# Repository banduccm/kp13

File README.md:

# Keypad #

This is an attempt to design a serviceable replacement the long-discontinued G13 "gameboard".

## PCB ##

The PCB design depends on symbols from a few libraries:

- <https://github.com/stormbard/Keyboard.pretty> for the hotswap switch footprints
- <https://github.com/drewgates/kb2040-kicad> for the Adafruit KB2040 footprint, symbol, and step file
- <https://grabcad.com/library/kailh-hotswap-mx-1> for the hot-swap socket step file (requires registration)

### Board Layout ###

The G13 had 22 "G" keys, 2 thumb keys, and an analog stick with a click (in addition to some other buttons not
important to this effort).

This initial project contains the main board with 22 keys and 2 pushbuttons intended to be used to switch
layers in QMK. It also includes a header with 2 rows and 6 columns for an expansion board (i.e, the thumb
buttons).

The KB2040 was selected due to easy availability, compatibility with the Pro Micro pinout, and a USB-C port.
Other Pro Micro-compatible boards may work, but take care to skip the D+/D- pins from the KB2040.

## Plates ##

The switch mounting plates for this project were initially designed using swillkb's
[Plate & Case Builder](http://builder.swillkb.com/) tool, then imported into qcad for manipulation.

Experimental baseplates for both the keypad and full-size thumb pod are included, as are 3d-printable spacers
to sit between the plates and PCB.

### Keyboard Layout ###

This layout is used by both the plate builder and the
[Keyboard Layout Editor](http://www.keyboard-layout-editor.com) tool:

```text
[{x:3}, "C0", "C1"],
["G1","G2","G3","G4","G5","G6","G7"],
["G8","G9","G10","G11","G12","G13","G14"],
[{x:0.75,w:1.25},"G15","G16","G17","G18",{w:1.25},"G19"],
[{x:1,w:2},"G20","G21",{w:2},"G22"],
[{x:8.75}, "Stick ↑"],
[{x:7.25}, "G23", "Stick ←", "Stick →"],
[{x:7}, "G24", {x:0.75}, "Stick ↓" ],
[{x:8}, "G25", "G26"]
```

For Via (with some extra design flavor), this is:

```text
[{x:3},"3,4","3,5"],
["0,0","0,1","0,2","0,3","0,4","0,5","1,0"],
["1,1","1,2","1,3","1,4","1,5","2,0","2,1"],
[{x:0.75,w:1.25},"2,2","2,3","2,4","2,5",{w:1.25},"3,0"],
[{x:1,w:2},"3,1","3,2",{w:2},"3,3"],
[{y:0.75,x:8.75,h:0.75},"4,0"],
[{y:-0.75,x:7.25},"5,0"],
[{y:-0.5,x:8.25,h:0.75},"4,1",{h:0.75},"4,3"],
[{y:-0.5,x:7},"5,1"],
[{y:-0.75,x:8.75,h:0.75},"4,2"],
[{y:-0.25,x:8},"5,2","5,3"]

```

 ## Parts ##

 For the first build, the following parts were used:

 ### Plate ###

 The place was ordered from [SendCutSend](https://sendcutsend.com/) in 1.6mm thick 5051 Aluminum.

 ### Electronics ###

 Initial parts were ordered from Adafruit:

- 30x [1N4148 diodes](https://www.adafruit.com/product/1641)
- 20x [6mm Tactile Button switch](https://www.adafruit.com/product/367)
- 40x [Kailh Switch Sockets for MX-compatible Mechanical Keys](https://www.adafruit.com/product/4958)
- 30x [Kailh Mechanical Key Switches - Linear Black](https://www.adafruit.com/product/4953)
- 1x [Adafruit KB2040](https://www.adafruit.com/product/5302)
- ~~1x [GMK Screw-in Stabilizers](https://1upkeyboards.com/shop/parts-and-tools/parts/gmk-screw-in-stabilizers/)~~ _Note: These ended up being incompatible with the plate, see v0.1.0 notes_
- 1x [Durock Plate Mount Stabilizers](https://1upkeyboards.com/shop/parts-and-tools/parts/durock-plate-mount-stabilizers-60-tkl-piano/)

### PCB ###

The PCB was ordered from PCBWay using their Kicad plugin.

## Version Notes ##

### v0.1.0 ###

Generally good news! The parts all fit as expected and the circuit works as designed. No reworks required to
have a functioning 22-key setup.

- The plate is not compatible with the PCB-mount stabilizers.
- The angle on the plate and the angle on the PCB are not the same. This is annoying, but not a functional
 problem.
- n-key rollover works (as expected), but note that QMK defaults to 6KRO. The default keymap uses switch C0
 on Layer 0 to toggle it.

### v0.1.1 ###

Instead of relying on trying to rely on external tools, all the mechanical bits were re-drawn in qcad, which
helpfully makes it extremely simple to import an exported .dxf from KiCAD for tracing and fit checking. The
stabilizer compatibility was not addressed (yet), but at least the angle between the PCB and plate(s) now
aligns.

## v0.2.0 Wishlist ##

During the mechanical design phase, some items were added as a wishlist for a potential second spin of the
"big" board:

- Smaller, optimized thumb-pod connector. Considering using a 1.27mm pitch 10-pin cable (Cortex-M SWD
  connector) to reduce mechanical size.
- Figure out how to use the kb2040's castellated pins to reduce z-height

## Thumb Pods ##

The thumb pod(s) incorporate a 4-way (with diagonals!) thumbstick and 0-4 buttons. There are 2 different
versions: regular (4x 1U MX switch, 1x thumbstick) and mini (2x microswitch, 1x thumbstick). The thumbstick
uses the same matrix positions on each version, so it is possible to populate multiple pods and swap between
them as desired.

The pods feature a notched edge for mounting square against the keypad PCB (or a case holding it). This
ensures the A/B/C/D positions of the thumbstick are square with the keypad.

### Thumbstick ###

- [ALPS RKJXM1015004](https://tech.alpsalpine.com/e/products/detail/RKJXM1015004/)

This thumbstick has 4 switches and can handle diagonal movements as well. It has a "stick click", but this
is not broken out as a dedicated pin, so it's unclear if it is compatible with QMK. In v0.1 of the thumb
pods, the "push" pins are not connected to the key matrix. The "push" pins _are_ on their own net, however,
so they could be hand-wired into the matrix if desired. The same thumbstick is used for both thumb pod
designs.

### Thumb Pod (full size) ###

The regular thumb pod uses the same MX hot-swap sockets and 1U keys as the main keypad to provide 4 switches
surrounding the thumbstick.

Experimental top and bottom plates are provided for the full-size thumb pod.

### Thumb Pod Mini ###

The mini thumb pod closely approximates the original G13 thumb section: two mouse-like microswitches and the
thumbstick. This version will require some sort of housing, as it's not really feasible to hit microswitch
actuators.

#### Electronics ####

- [Kailh GM Microswitch](https://www.kailhswitch.com/micro-switches/mouse-micro-switches/high-click-life-gaming-micro-mouse-switch.html)

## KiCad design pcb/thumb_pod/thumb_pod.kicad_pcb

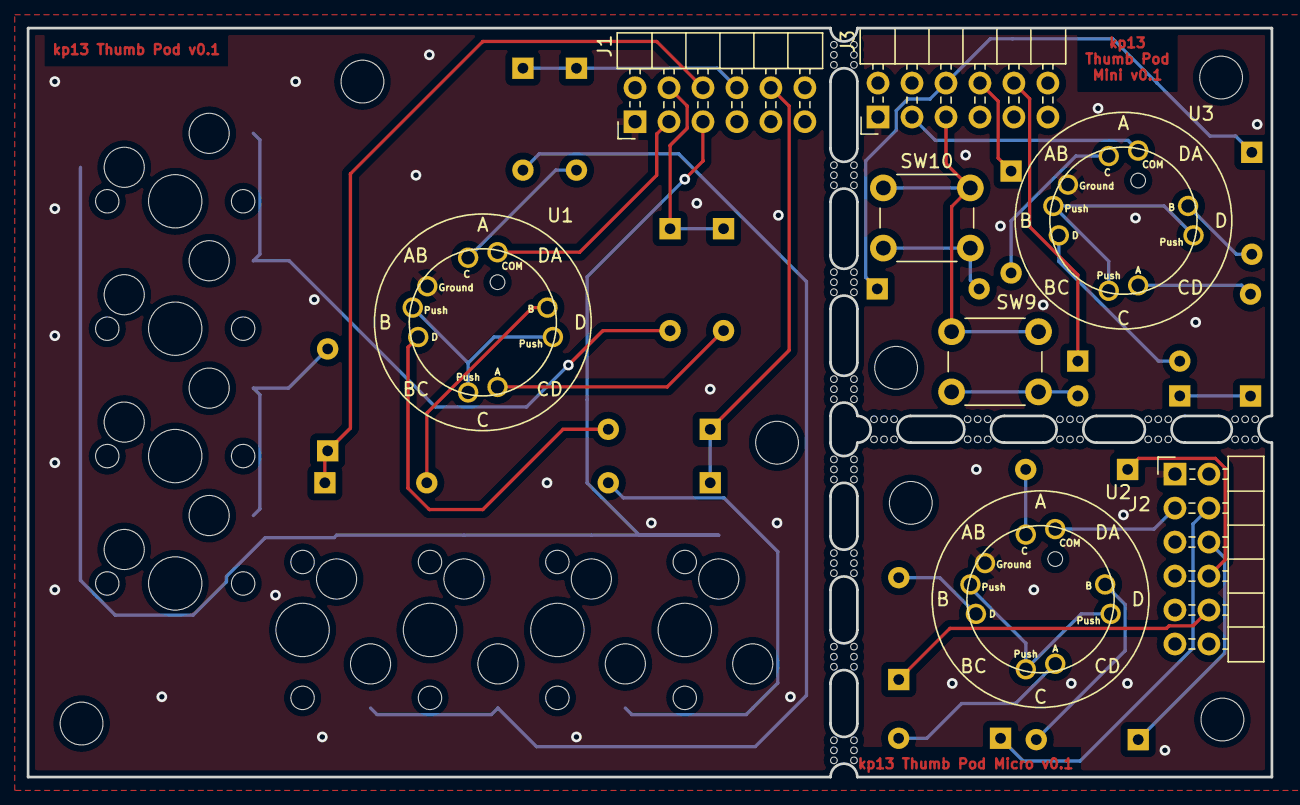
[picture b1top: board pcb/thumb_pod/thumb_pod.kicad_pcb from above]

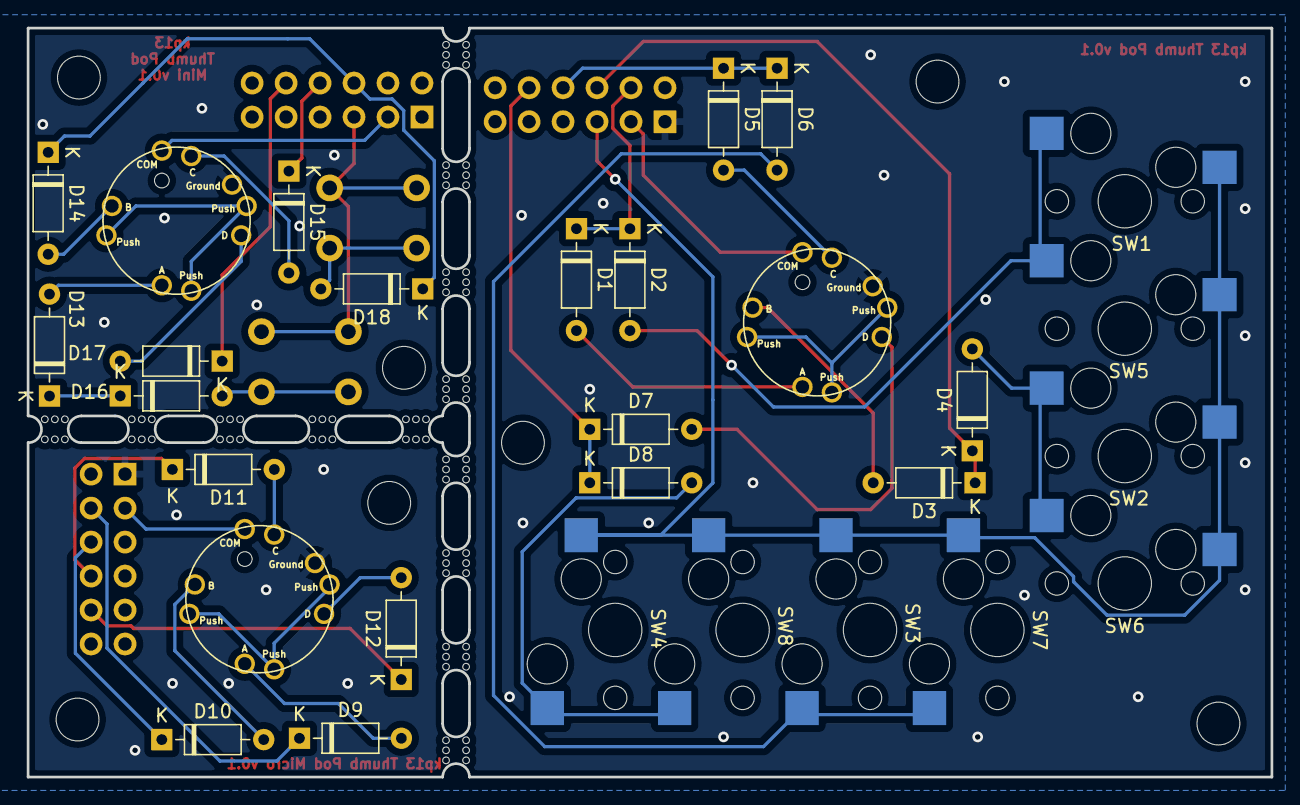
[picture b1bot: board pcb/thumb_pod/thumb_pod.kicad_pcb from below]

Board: 2 copper layers, 93.0 x 56.0 mm, 54 parts (18 on the bottom side), 28 nets.

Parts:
D1, D2, D3, D4, D5, D6, D7, D8, D9, D10, D11, D12, D13, D14, D15, D16, D17, D18: 1N4148; D_DO-35_SOD27_P7.62mm_Horizontal
H1, H2, H3, H4, H5, H6, H7: MountingHole; MountingHole_3.2mm_M3
J1, J2, J3: Conn_02x06_Odd_Even; PinHeader_2x06_P2.54mm_Horizontal
SW1, SW2, SW3, SW4, SW5, SW6, SW7, SW8: SW_Push; MXOnly-1U-Hotswap
SW9, SW10: SW_Push; SW_PUSH_6mm
U1, U2, U3: RKJXM1015004
mouse-bite-2mm-slot, mouse-bite-2mm-slot#2, mouse-bite-2mm-slot#3, mouse-bite-2mm-slot#4, mouse-bite-2mm-slot#5, mouse-bite-2mm-slot#6, mouse-bite-2mm-slot#7, mouse-bite-2mm-slot#8, mouse-bite-2mm-slot#9, mouse-bite-2mm-slot#10, mouse-bite-2mm-slot#11, mouse-bite-2mm-slot#12, mouse-bite-2mm-slot#13: VAL**; mouse-bite-2mm-slot

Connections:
/3.3v: J1.2, J2.2, J3.2
/Col0: D1.1 (K), D2.1 (K), D9.1 (K), D13.1 (K), D16.1 (K), J1.4, J2.4, J3.4
/Col1: D3.1 (K), D4.1 (K), D10.1 (K), D14.1 (K), D18.1 (K), J1.6, J2.6, J3.6
/Col2: D5.1 (K), D6.1 (K), D11.1 (K), D15.1 (K), J1.8, J2.8, J3.8
/Col3: D7.1 (K), D8.1 (K), D12.1 (K), D17.1 (K), J1.10, J2.10, J3.10
/Col4: J1.12, J2.12, J3.12
/Col5: J1.11, J2.11, J3.11
/GND: J1.1, J2.1, J3.1, U1.6 (Ground), U2.6 (Ground), U3.6 (Ground)
/Row4: J1.3, J2.3, J3.3, U1.1 (COM), U2.1 (COM), U3.1 (COM)
/Row5: J1.5, J2.5, J3.5, SW1.1, SW2.1, SW3.1, SW4.1, SW5.1, SW6.1, SW7.1, SW8.1, SW9.1, SW10.1
unnamed: D1.2 (A), U1.4 (A)
unnamed: D2.2 (A), SW1.2, SW5.2
unnamed: D3.2 (A), U1.2 (B)
unnamed: D4.2 (A), SW2.2, SW6.2
unnamed: D5.2 (A), U1.7 (C)
unnamed: D6.2 (A), SW3.2, SW7.2
unnamed: D7.2 (A), U1.5 (D)
unnamed: D8.2 (A), SW4.2, SW8.2
unnamed: D9.2 (A), U2.4 (A)
unnamed: D10.2 (A), U2.2 (B)
unnamed: D11.2 (A), U2.7 (C)
unnamed: D12.2 (A), U2.5 (D)
unnamed: D13.2 (A), U3.4 (A)
unnamed: D14.2 (A), U3.2 (B)
unnamed: D15.2 (A), U3.7 (C)
unnamed: D16.2 (A), SW9.2
unnamed: D17.2 (A), U3.5 (D)
unnamed: D18.2 (A), SW10.2

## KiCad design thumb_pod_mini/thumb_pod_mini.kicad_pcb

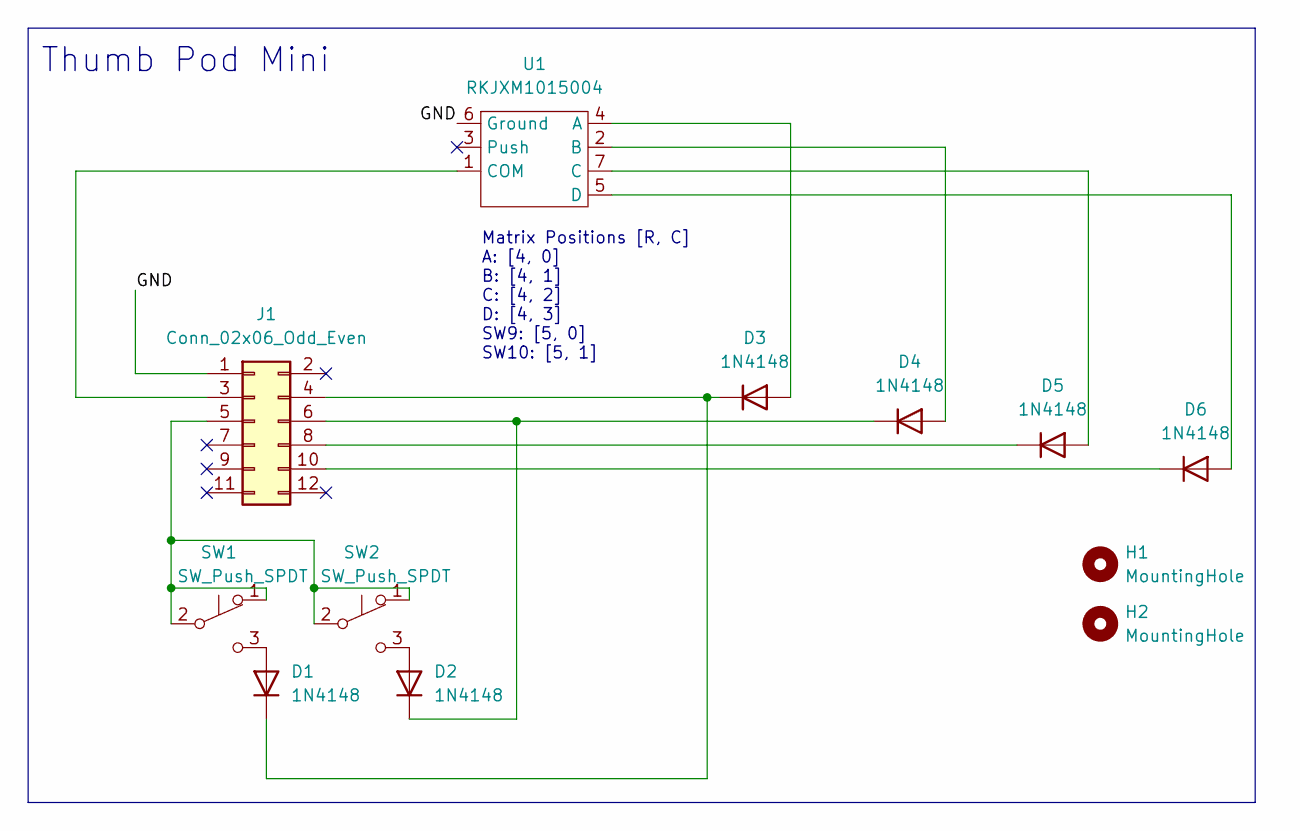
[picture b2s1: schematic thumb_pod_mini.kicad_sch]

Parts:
D1, D2, D3, D4, D5, D6: 1N4148; D_DO-35_SOD27_P7.62mm_Horizontal
H1, H2: MountingHole; MountingHole_3.2mm_M3
J1: Conn_02x06_Odd_Even; PinHeader_2x06_P2.54mm_Horizontal
SW1, SW2: SW_Push_SPDT; kailh_gm_microswitch
U1: RKJXM1015004

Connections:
/GND: J1.1, U1.6 (Ground)
unnamed: D1.1 (K), D3.1 (K), J1.4
unnamed: D1.2 (A), SW1.3 (C)
unnamed: D2.1 (K), D4.1 (K), J1.6
unnamed: D2.2 (A), SW2.3 (C)
unnamed: D3.2 (A), U1.4 (A)
unnamed: D4.2 (A), U1.2 (B)
unnamed: D5.1 (K), J1.8
unnamed: D5.2 (A), U1.7 (C)
unnamed: D6.1 (K), J1.10
unnamed: D6.2 (A), U1.5 (D)
unnamed: J1.3, U1.1 (COM)
unnamed: J1.5, SW1.1 (A), SW1.2 (B), SW2.1 (A), SW2.2 (B)

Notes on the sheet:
Matrix Positions [R, C] A: [4, 0] B: [4, 1] C: [4, 2] D: [4, 3] SW9: [5, 0] SW10: [5, 1]
Thumb Pod Mini

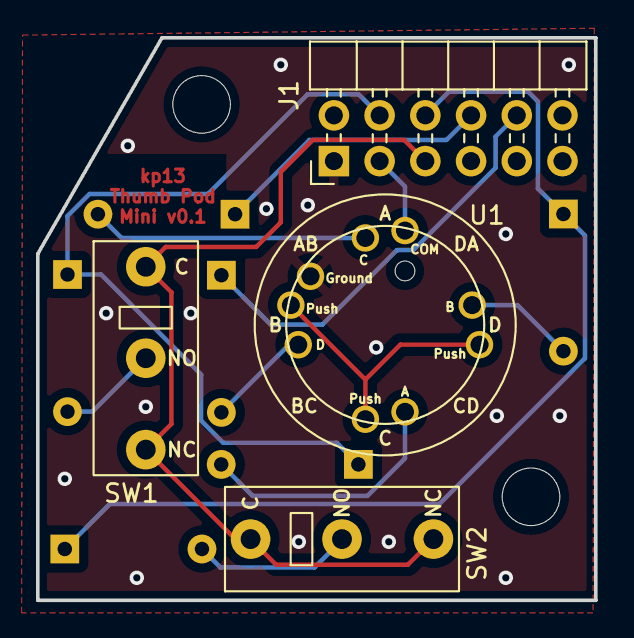
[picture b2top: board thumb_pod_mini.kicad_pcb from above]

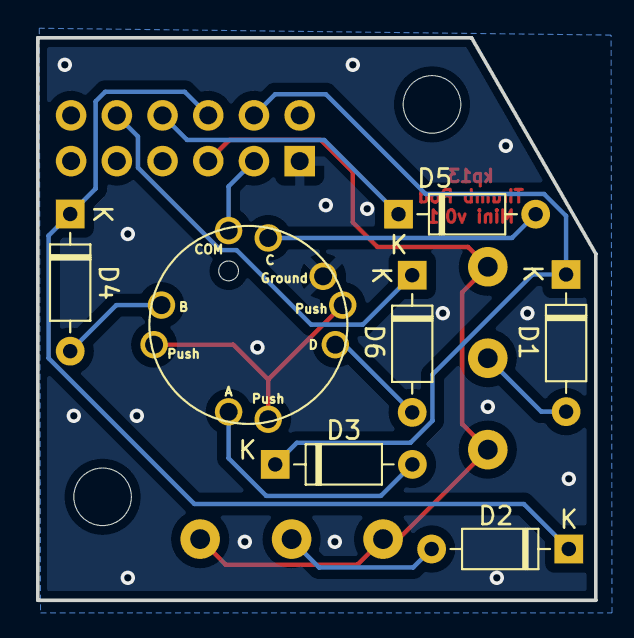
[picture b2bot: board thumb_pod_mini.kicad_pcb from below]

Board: 2 copper layers, 31.0 x 31.2 mm, 12 parts (6 on the bottom side), 13 nets.

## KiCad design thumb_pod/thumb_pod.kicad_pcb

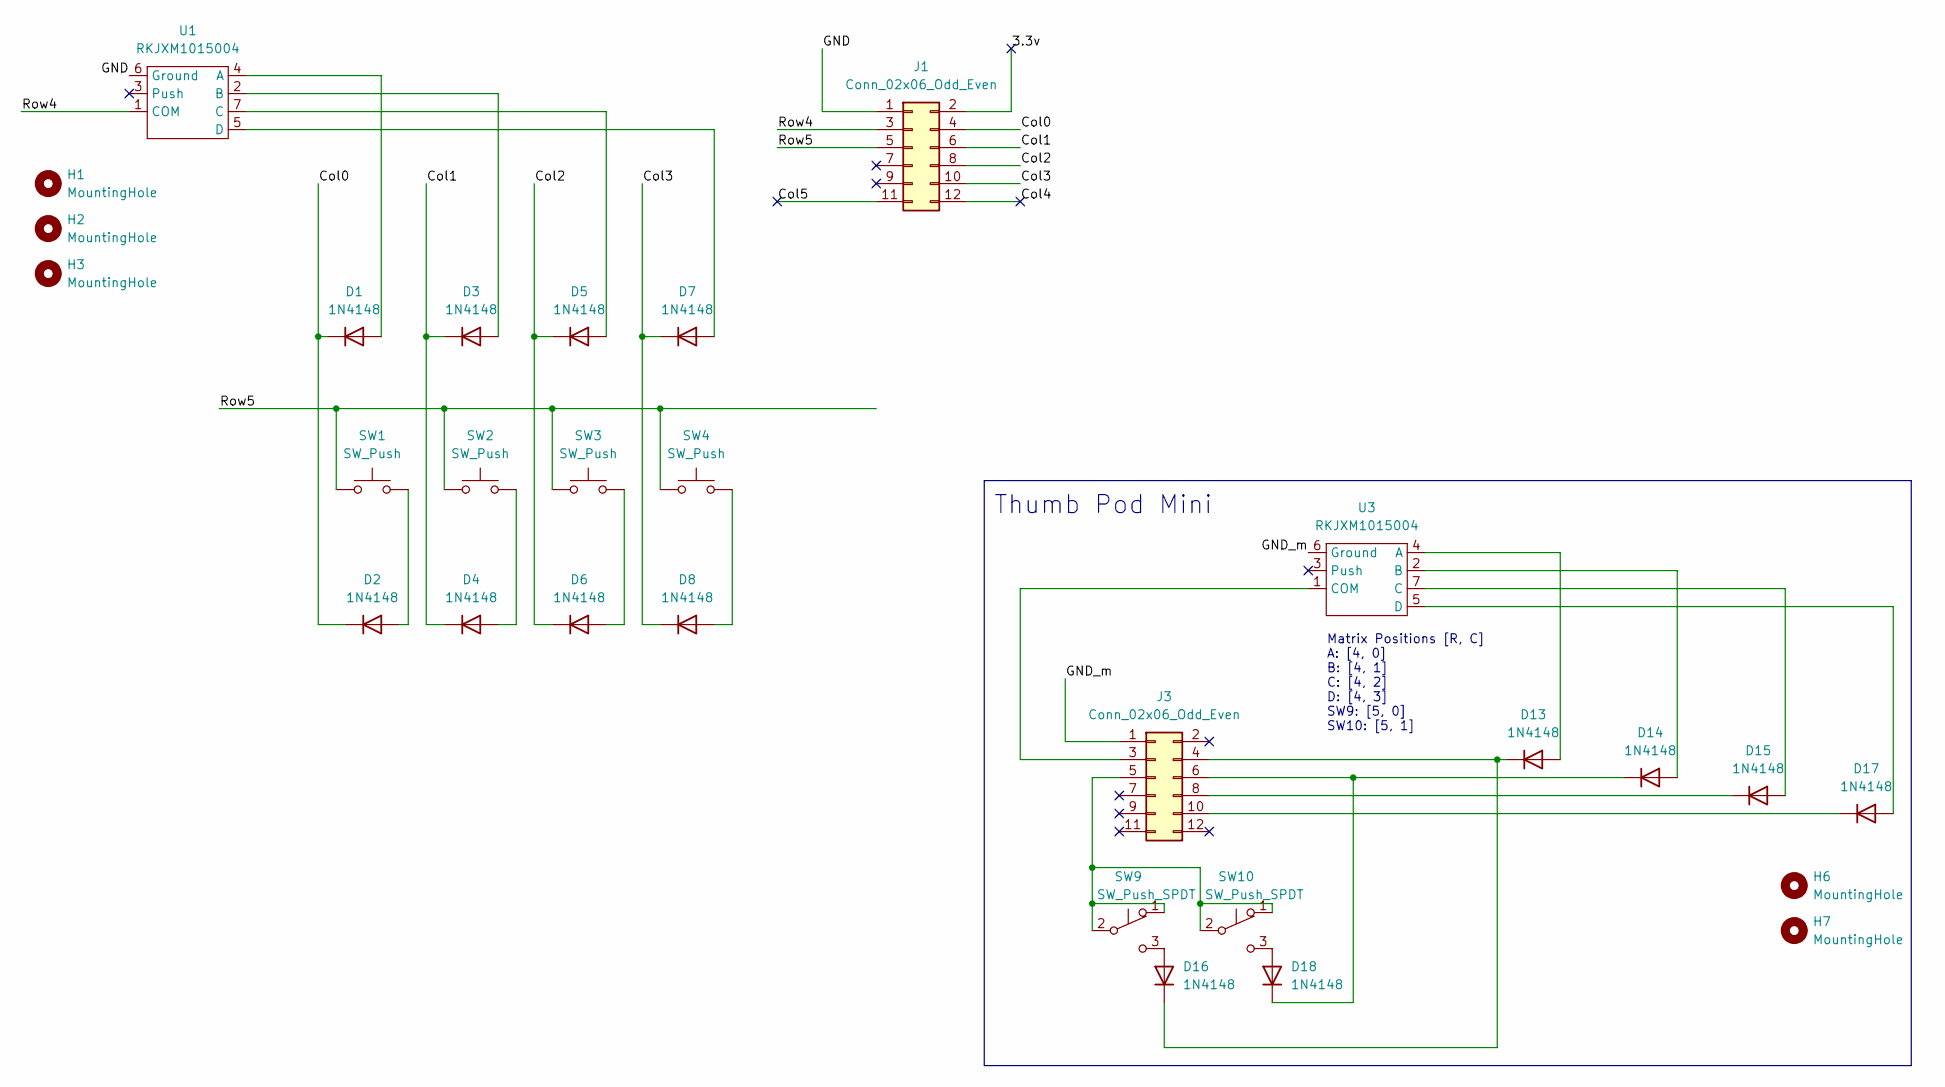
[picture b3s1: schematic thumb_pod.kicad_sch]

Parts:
D1, D2, D3, D4, D5, D6, D7, D8, D13, D14, D15, D16, D17, D18: 1N4148; D_DO-35_SOD27_P7.62mm_Horizontal
H1, H2, H3, H6, H7: MountingHole; MountingHole_3.2mm_M3
J1, J3: Conn_02x06_Odd_Even; PinHeader_2x06_P2.54mm_Horizontal
SW1, SW2, SW3, SW4: SW_Push; MXOnly-1U-Hotswap
SW9, SW10: SW_Push_SPDT; kailh_gm_microswitch
U1, U3: RKJXM1015004

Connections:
/3.3v: J1.2
/Col0: D1.1 (K), D2.1 (K), J1.4
/Col1: D3.1 (K), D4.1 (K), J1.6
/Col2: D5.1 (K), D6.1 (K), J1.8
/Col3: D7.1 (K), D8.1 (K), J1.10
/Col4: J1.12
/Col5: J1.11
/GND: J1.1, U1.6 (Ground)
/GND_m: J3.1, U3.6 (Ground)
/Row4: J1.3, U1.1 (COM)
/Row5: J1.5, SW1.1, SW2.1, SW3.1, SW4.1
unnamed: D1.2 (A), U1.4 (A)
unnamed: D2.2 (A), SW1.2
unnamed: D3.2 (A), U1.2 (B)
unnamed: D4.2 (A), SW2.2
unnamed: D5.2 (A), U1.7 (C)
unnamed: D6.2 (A), SW3.2
unnamed: D7.2 (A), U1.5 (D)
unnamed: D8.2 (A), SW4.2
unnamed: D13.1 (K), D16.1 (K), J3.4
unnamed: D13.2 (A), U3.4 (A)
unnamed: D14.1 (K), D18.1 (K), J3.6
unnamed: D14.2 (A), U3.2 (B)
unnamed: D15.1 (K), J3.8
unnamed: D15.2 (A), U3.7 (C)
unnamed: D16.2 (A), SW9.3 (C)
unnamed: D17.1 (K), J3.10
unnamed: D17.2 (A), U3.5 (D)
unnamed: D18.2 (A), SW10.3 (C)
unnamed: J3.3, U3.1 (COM)
unnamed: J3.5, SW9.1 (A), SW9.2 (B), SW10.1 (A), SW10.2 (B)

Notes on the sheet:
Thumb Pod Mini
Matrix Positions [R, C] A: [4, 0] B: [4, 1] C: [4, 2] D: [4, 3] SW9: [5, 0] SW10: [5, 1]

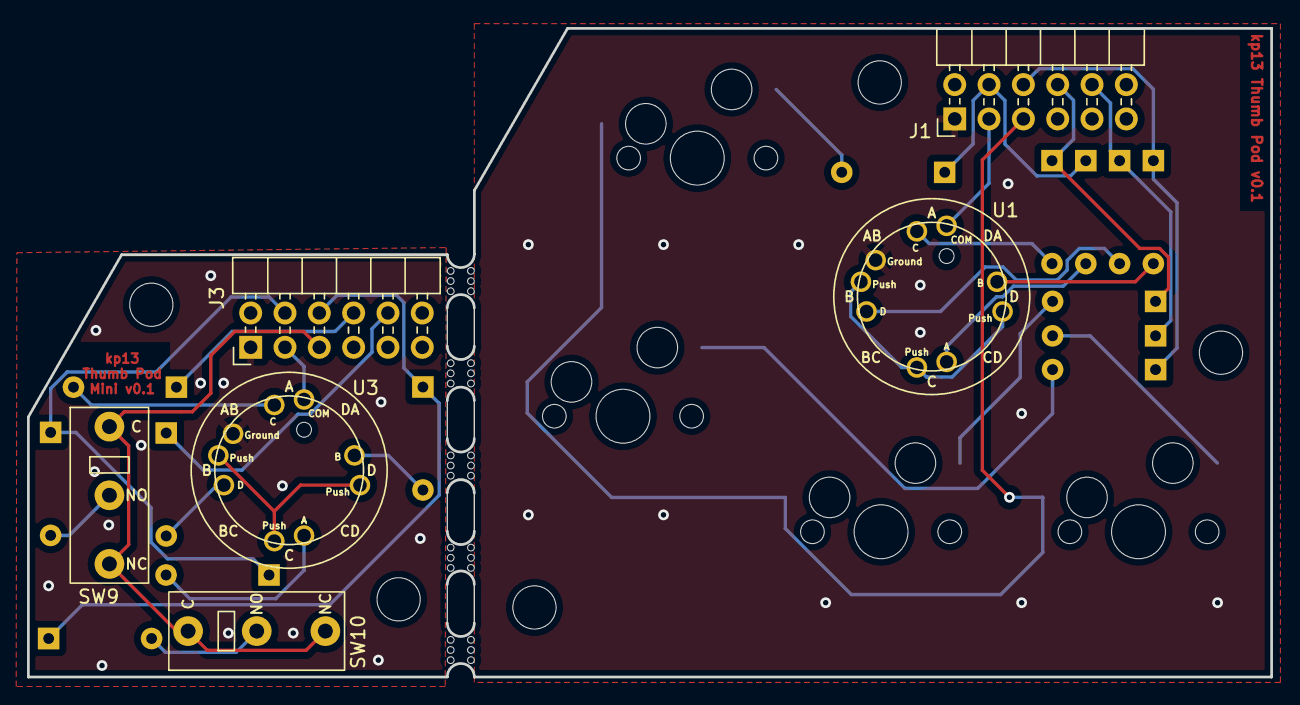
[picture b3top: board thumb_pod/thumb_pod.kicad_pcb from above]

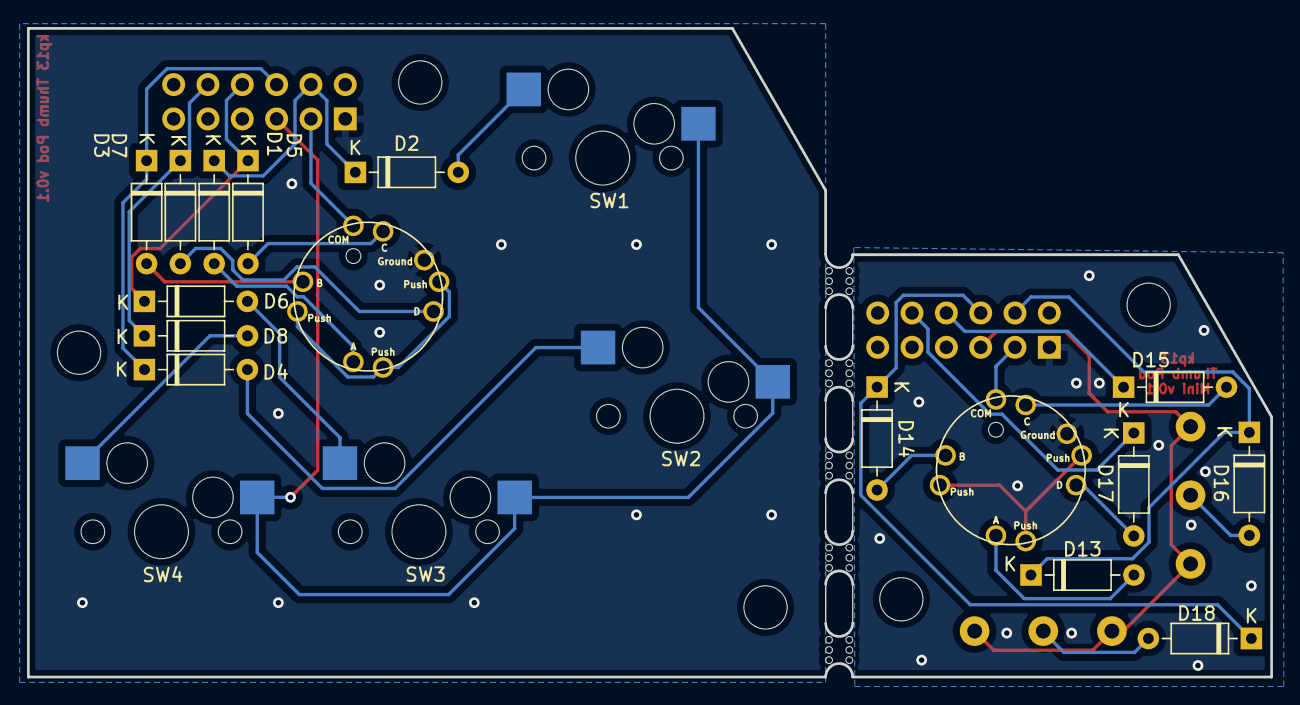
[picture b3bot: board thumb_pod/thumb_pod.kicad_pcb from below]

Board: 2 copper layers, 92.0 x 48.0 mm, 34 parts (14 on the bottom side), 28 nets.

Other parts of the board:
mouse-bite-2mm-slot, mouse-bite-2mm-slot#2, mouse-bite-2mm-slot#3, mouse-bite-2mm-slot#4, mouse-bite-2mm-slot#5: VAL**; mouse-bite-2mm-slot

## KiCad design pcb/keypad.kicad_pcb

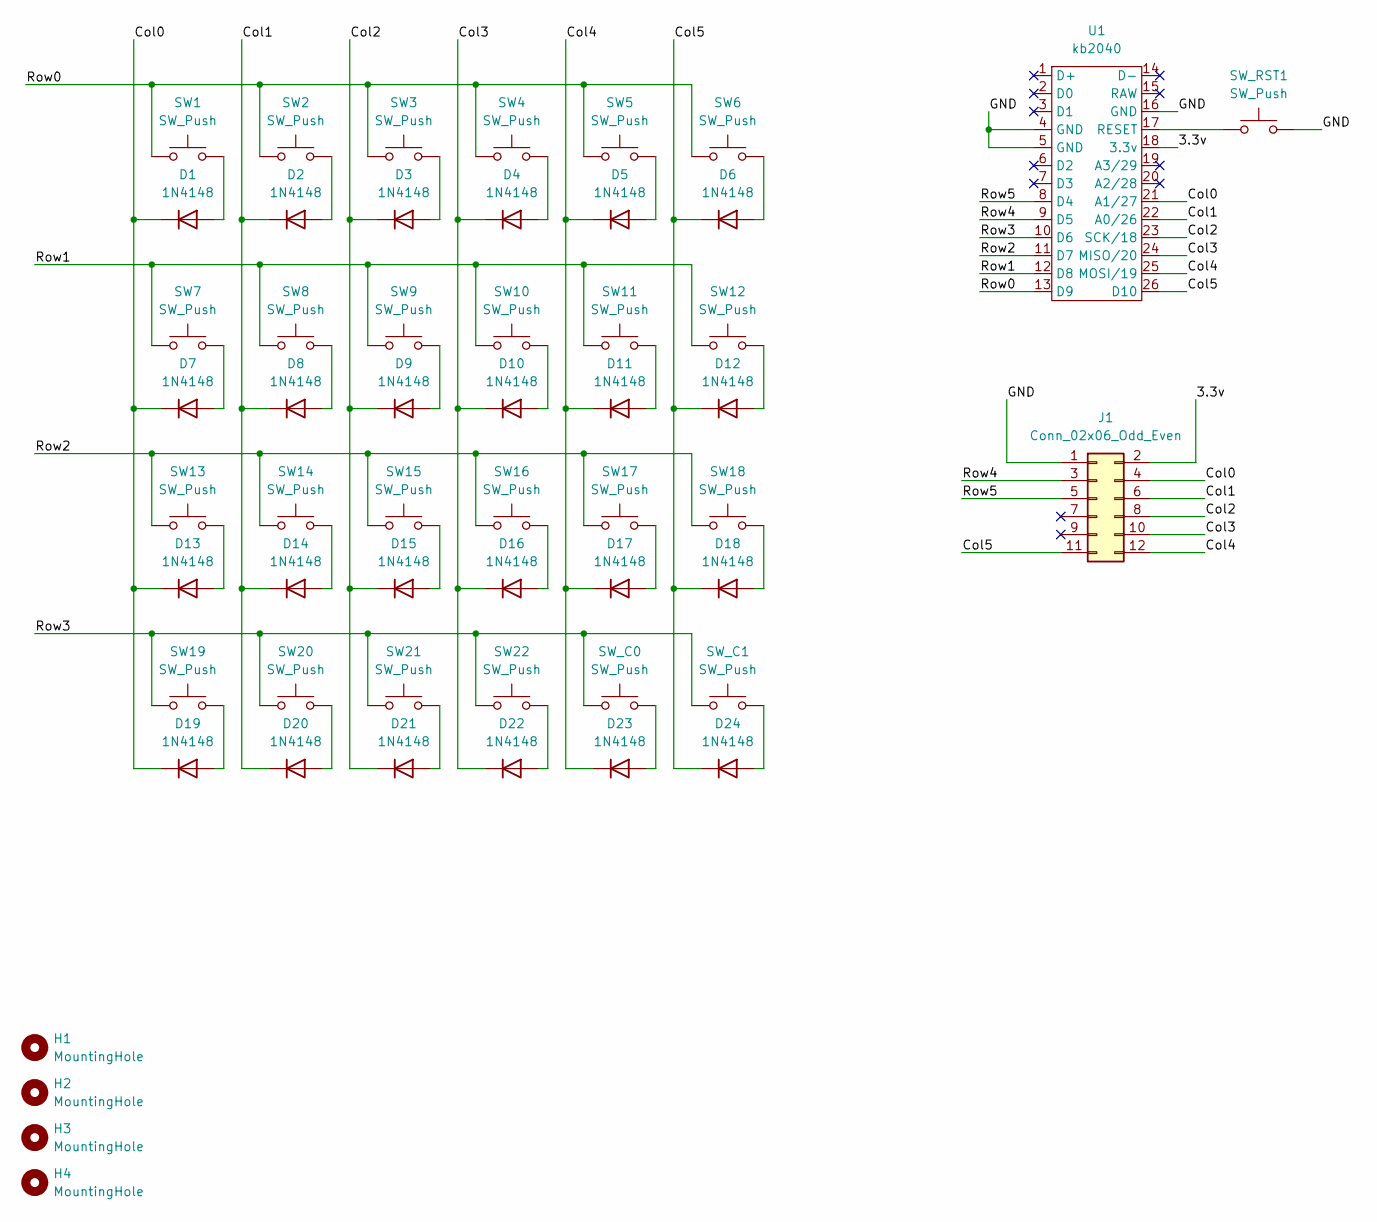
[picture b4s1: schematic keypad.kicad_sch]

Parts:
D1, D2, D3, D4, D5, D6, D7, D8, D9, D10, D11, D12, D13, D14, D15, D16, D17, D18, D19, D20, D21, D22, D23, D24: 1N4148; D_DO-35_SOD27_P7.62mm_Horizontal
H1, H2, H3, H4: MountingHole; MountingHole_3.2mm_M3
J1: Conn_02x06_Odd_Even; PinHeader_2x06_P2.54mm_Horizontal
SW1, SW2, SW3, SW4, SW5, SW6, SW7, SW8, SW9, SW10, SW11, SW12, SW13, SW14, SW16, SW17, SW18, SW21: SW_Push; MXOnly-1U-Hotswap
SW15, SW19: SW_Push; MXOnly-1.25U-Hotswap
SW20, SW22: SW_Push; MXOnly-2U-Hotswap
SW_C0, SW_C1: SW_Push; SW_PUSH_6mm_H7.3mm
SW_RST1: SW_Push; SW_PUSH_6mm_H7.3mm
U1: kb2040

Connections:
/3.3v: J1.2, U1.18 (3.3v)
/Col0: D1.1 (K), D7.1 (K), D13.1 (K), D19.1 (K), J1.4, U1.21 (A1/27)
/Col1: D2.1 (K), D8.1 (K), D14.1 (K), D20.1 (K), J1.6, U1.22 (A0/26)
/Col2: D3.1 (K), D9.1 (K), D15.1 (K), D21.1 (K), J1.8, U1.23 (SCK/18)
/Col3: D4.1 (K), D10.1 (K), D16.1 (K), D22.1 (K), J1.10, U1.24 (MISO/20)
/Col4: D5.1 (K), D11.1 (K), D17.1 (K), D23.1 (K), J1.12, U1.25 (MOSI/19)
/Col5: D6.1 (K), D12.1 (K), D18.1 (K), D24.1 (K), J1.11, U1.26 (D10)
/GND: J1.1, SW_RST1.2, U1.4 (GND), U1.5 (GND), U1.16 (GND)
/Row0: SW1.1, SW2.1, SW3.1, SW4.1, SW5.1, SW6.1, U1.13 (D9)
/Row1: SW7.1, SW8.1, SW9.1, SW10.1, SW11.1, SW12.1, U1.12 (D8)
/Row2: SW13.1, SW14.1, SW15.1, SW16.1, SW17.1, SW18.1, U1.11 (D7)
/Row3: SW19.1, SW20.1, SW21.1, SW22.1, SW_C0.1, SW_C1.1, U1.10 (D6)
/Row4: J1.3, U1.9 (D5)
/Row5: J1.5, U1.8 (D4)
unnamed: D1.2 (A), SW1.2
unnamed: D2.2 (A), SW2.2
unnamed: D3.2 (A), SW3.2
unnamed: D4.2 (A), SW4.2
unnamed: D5.2 (A), SW5.2
unnamed: D6.2 (A), SW6.2
unnamed: D7.2 (A), SW7.2
unnamed: D8.2 (A), SW8.2
unnamed: D9.2 (A), SW9.2
unnamed: D10.2 (A), SW10.2
unnamed: D11.2 (A), SW11.2
unnamed: D12.2 (A), SW12.2
unnamed: D13.2 (A), SW13.2
unnamed: D14.2 (A), SW14.2
unnamed: D15.2 (A), SW15.2
unnamed: D16.2 (A), SW16.2
unnamed: D17.2 (A), SW17.2
unnamed: D18.2 (A), SW18.2
unnamed: D19.2 (A), SW19.2
unnamed: D20.2 (A), SW20.2
unnamed: D21.2 (A), SW21.2
unnamed: D22.2 (A), SW22.2
unnamed: D23.2 (A), SW_C0.2
unnamed: D24.2 (A), SW_C1.2
unnamed: SW_RST1.1, U1.17 (RESET)

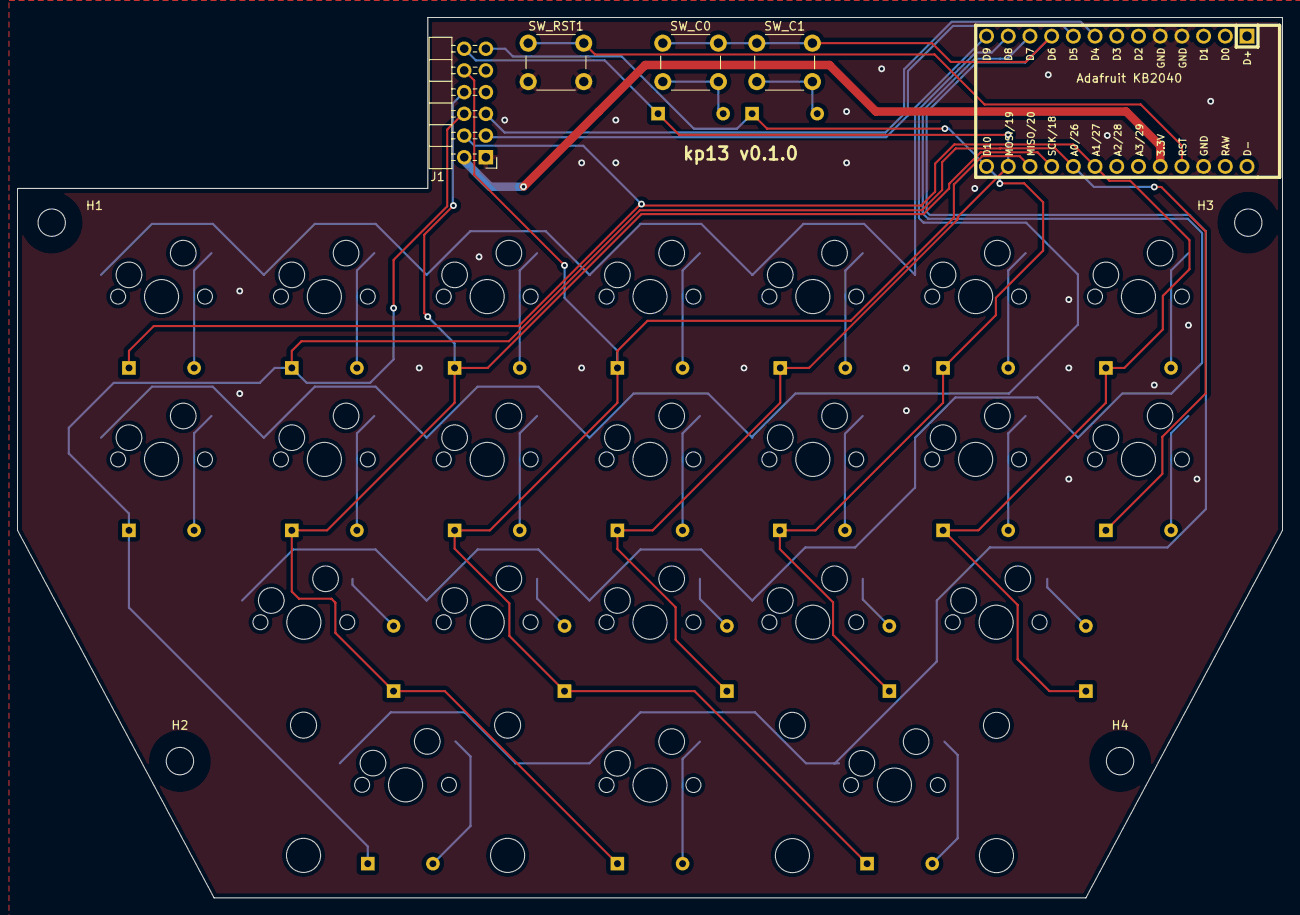
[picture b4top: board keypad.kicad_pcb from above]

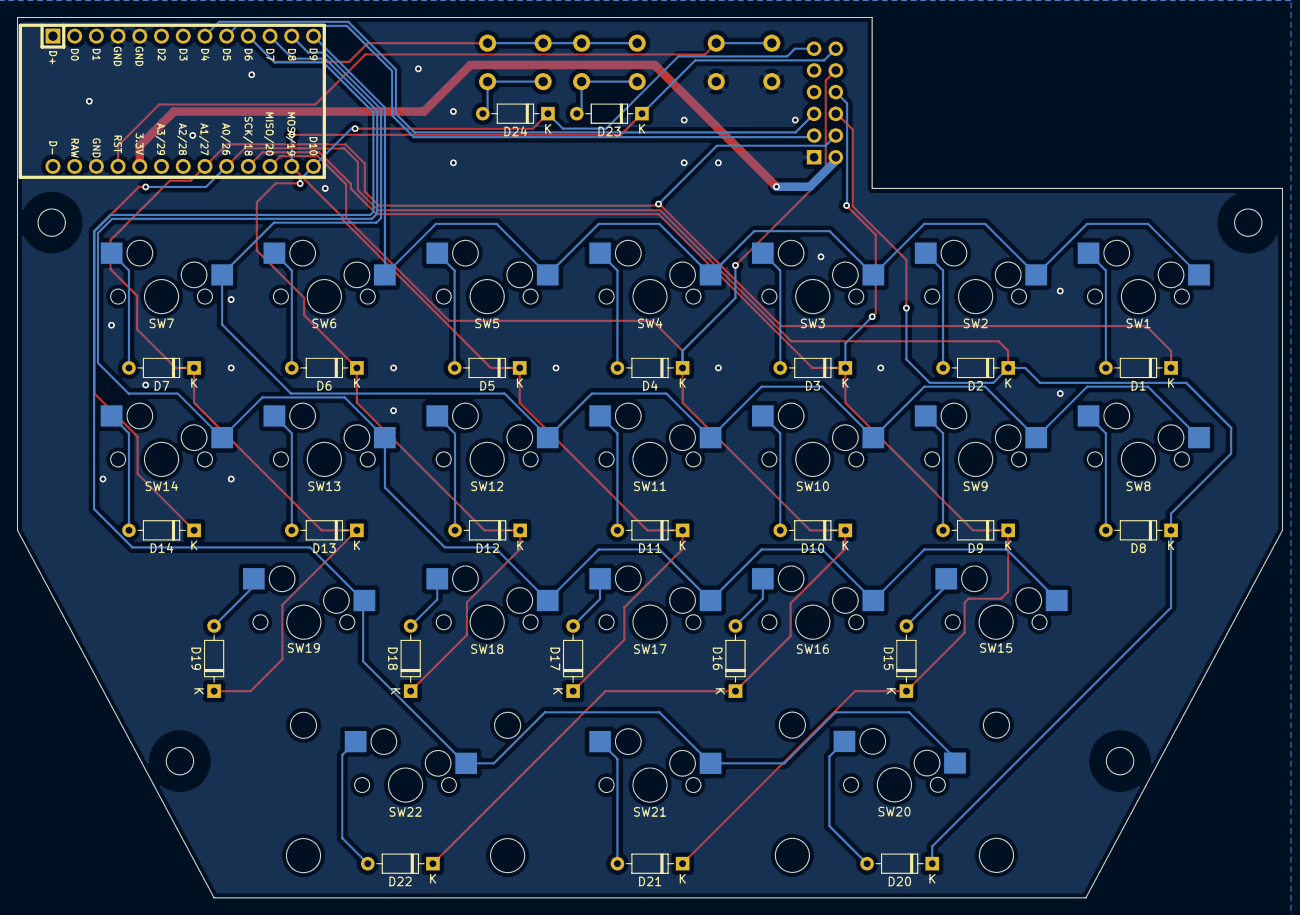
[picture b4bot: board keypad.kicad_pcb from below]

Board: 2 copper layers, 148.0 x 103.0 mm, 55 parts (24 on the bottom side), 39 nets.

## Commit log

2022-07-12 - Initial board design, layout - Initial readme
2022-07-12 - Added a reset button for the controller - Moved the through-hole diodes to not interfere with the switches
2022-12-04 - Added plate details - Fixed the spacing of non-1U keys on the PCB layout
2022-12-07 - Updated readme with parts
2022-12-07 - Switched to the KB2040 - Modified the pin header to remove some silk screen sections
2022-12-10 Added QMK board definition files
2022-12-11 Moved necessary symbols into the project library - (I don't know if this comes with license issues; if there's a problem let me know and I can remove the symbols)
2022-12-13 - Marked NC pins - Updated diode symbols
2022-12-22 - Updated readme with initial build notes - Added additional layers to the keymap for testing
2023-01-08 - First attempt at a thumb pod design
2023-01-15 - Added multiple positions for each switch to allow for tweaking
2023-01-15 - Added a board label and version
2023-01-19 - Added a preliminary "mini" thumb pod with only the directional stick - Added mouse bite footprint from Panelization.pretty
2023-01-19 - Added experimental alternate layouts for the thumb pod - Attempted some DIY panelization
2023-01-21 - Updated the "mini" thumb pod with an angled PCB edge
2023-01-22 - Rearranged sub-boards to (hopefully) make manufacturing easier - Fixed the schematic to better isolate each thumb pod version
2023-01-22 - Rearranged repository - Updated readme with thumb pod details
2023-01-31 - Removed "micro" thumb pod - Added kailh gm microswitch footprint - Switch to kail gm microswitches for the "mini" thumb pod - Reduced size of joystick silkscreen
2023-01-31 - Updated the kailh gm switch footprint to match the SPDT symbol - Updated the mini thumb pod switches to allow them to be placed in either orientation
2023-02-01 - Added models for the thumbstick and microswitch - thumbstick: https://tech.alpsalpine.com/e/products/detail/RKJXM1015004/ - microswitch: https://grabcad.com/library/tiny-switch-kailh-mouse-1
2023-02-02 - Abandoned the multi-position 1U switch experiment - Added a notch to the thumb pod (normal sized) - Adjusted button placement on the larger thumb pod based on testing - Updated the readme
2023-02-12 - Split the thumb pod PCBs
2024-09-30 - BOM update to reflect the actual stabilizers used
2024-09-30 - Updated keymap and matrix for the default thumb pod - Added a thumb pod plate design
2024-09-30 - Experimental plate updates - (untested) base plates for the keypad and larger thumb pod - (untested) keypad plate update with correct angles and slightly enlarged key cuts
2024-10-05 - Updated readme - Rounded thumb pod plate corners to be consistent - Initial work on top/bottom keypad plate spacers
2024-10-06 - Continued work on mechanical bits - Added a plate readme - Added .stls for the spacers - Added thumb pod spacer files
2024-10-06 - Corrected cutouts for the keypad baseplate spacer
2024-10-06 - Additional keypad/baseplate spacer fixes
2024-10-06 - Updated cached qmk files (thanks, brandon!) - Added a cached via layout file - Added a better qmk readme
